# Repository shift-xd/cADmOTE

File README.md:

# cADmOTE is a 3d accelormeter powered remote to rotate , manupulate and view your 3d models in all cad !

## cADmOTE is one of my creations for HACK CLUB BLUEPRINT event 

### Cadmote uses an xiao Rp2040 board an accelrometer and 5 buttons you can program 

## here's some images for reference & Demo 

### Inside 3d Enclosure 

### Image of cADmOTE's PCB 

### Image Of PCB & Schematics itself

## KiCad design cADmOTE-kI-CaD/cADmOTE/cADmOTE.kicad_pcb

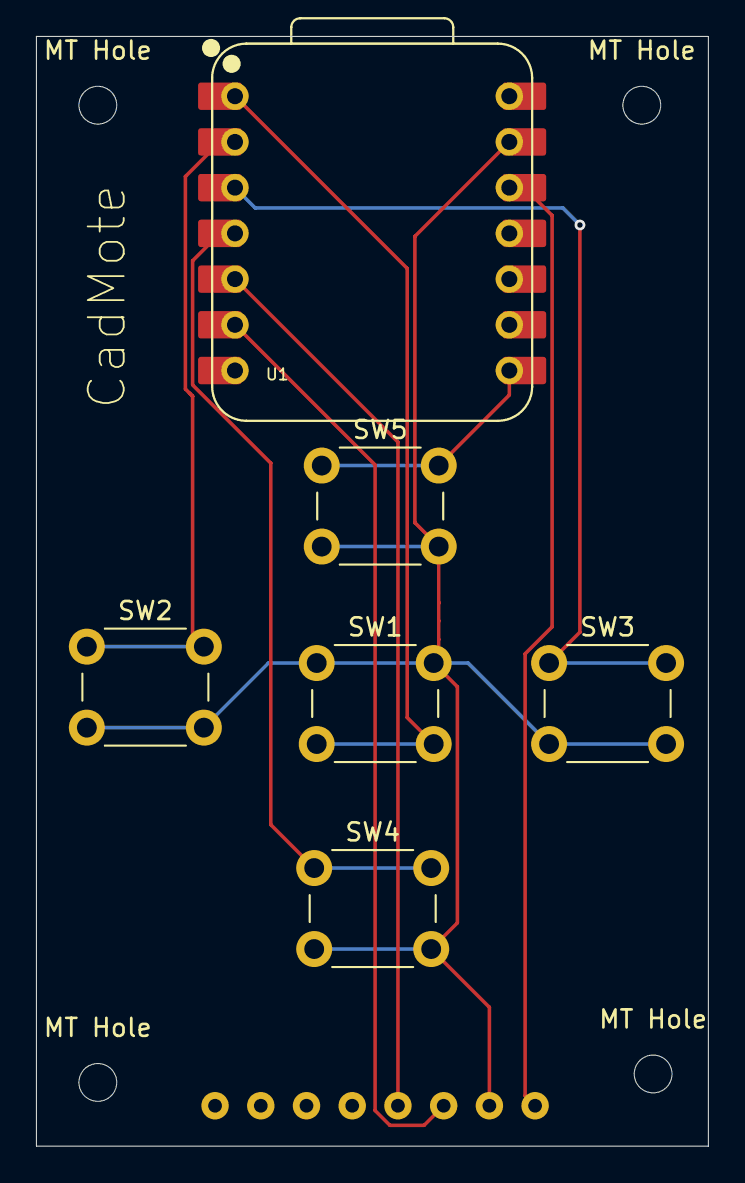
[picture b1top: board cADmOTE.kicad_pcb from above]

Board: 2 copper layers, 37.3 x 61.7 mm, 11 parts (1 on the bottom side), 9 nets.

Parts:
MT Hole: MountingHole_2.1mm
MT Hole#2, MT Hole#3, MT Hole#4: MountingHole_2.1mm
SW1, SW2, SW3, SW4, SW5: SW_Push; SW_PUSH_6mm
U1: Seeed Studio XIAO nRF52840; XIAO-RP2040-DIP
U3: module_mpu6050

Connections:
unnamed: U1.12 (3V3), U3.1 (VCC)
unnamed: SW1.2, U1.1 (P0.02_A0_D0)
unnamed: SW2.1, U1.2 (P0.03_A1_D1)
unnamed: U1.5 (P0.04_A4_D4_SDA), U3.4 (SDA)
unnamed: U1.6 (P0.05_A5_D5_SCL), U3.3 (SCL)
unnamed: SW3.1, U1.3 (P0.28_A2_D2)
unnamed: SW4.1, U1.4 (P0.29_A3_D3)
unnamed: SW5.1, U1.8 (P1.12_D7_RX)
unnamed: SW1.1, SW2.2, SW3.2, SW4.2, SW5.2, U1.13 (GND), U3.2 (GND)

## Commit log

2025-12-04 fOR bLUEprint
2025-12-04 bLUEpRINT ? ? :{
2025-12-04 Create ARDUINO IDE
2025-12-06 Update ARDUINO IDE
